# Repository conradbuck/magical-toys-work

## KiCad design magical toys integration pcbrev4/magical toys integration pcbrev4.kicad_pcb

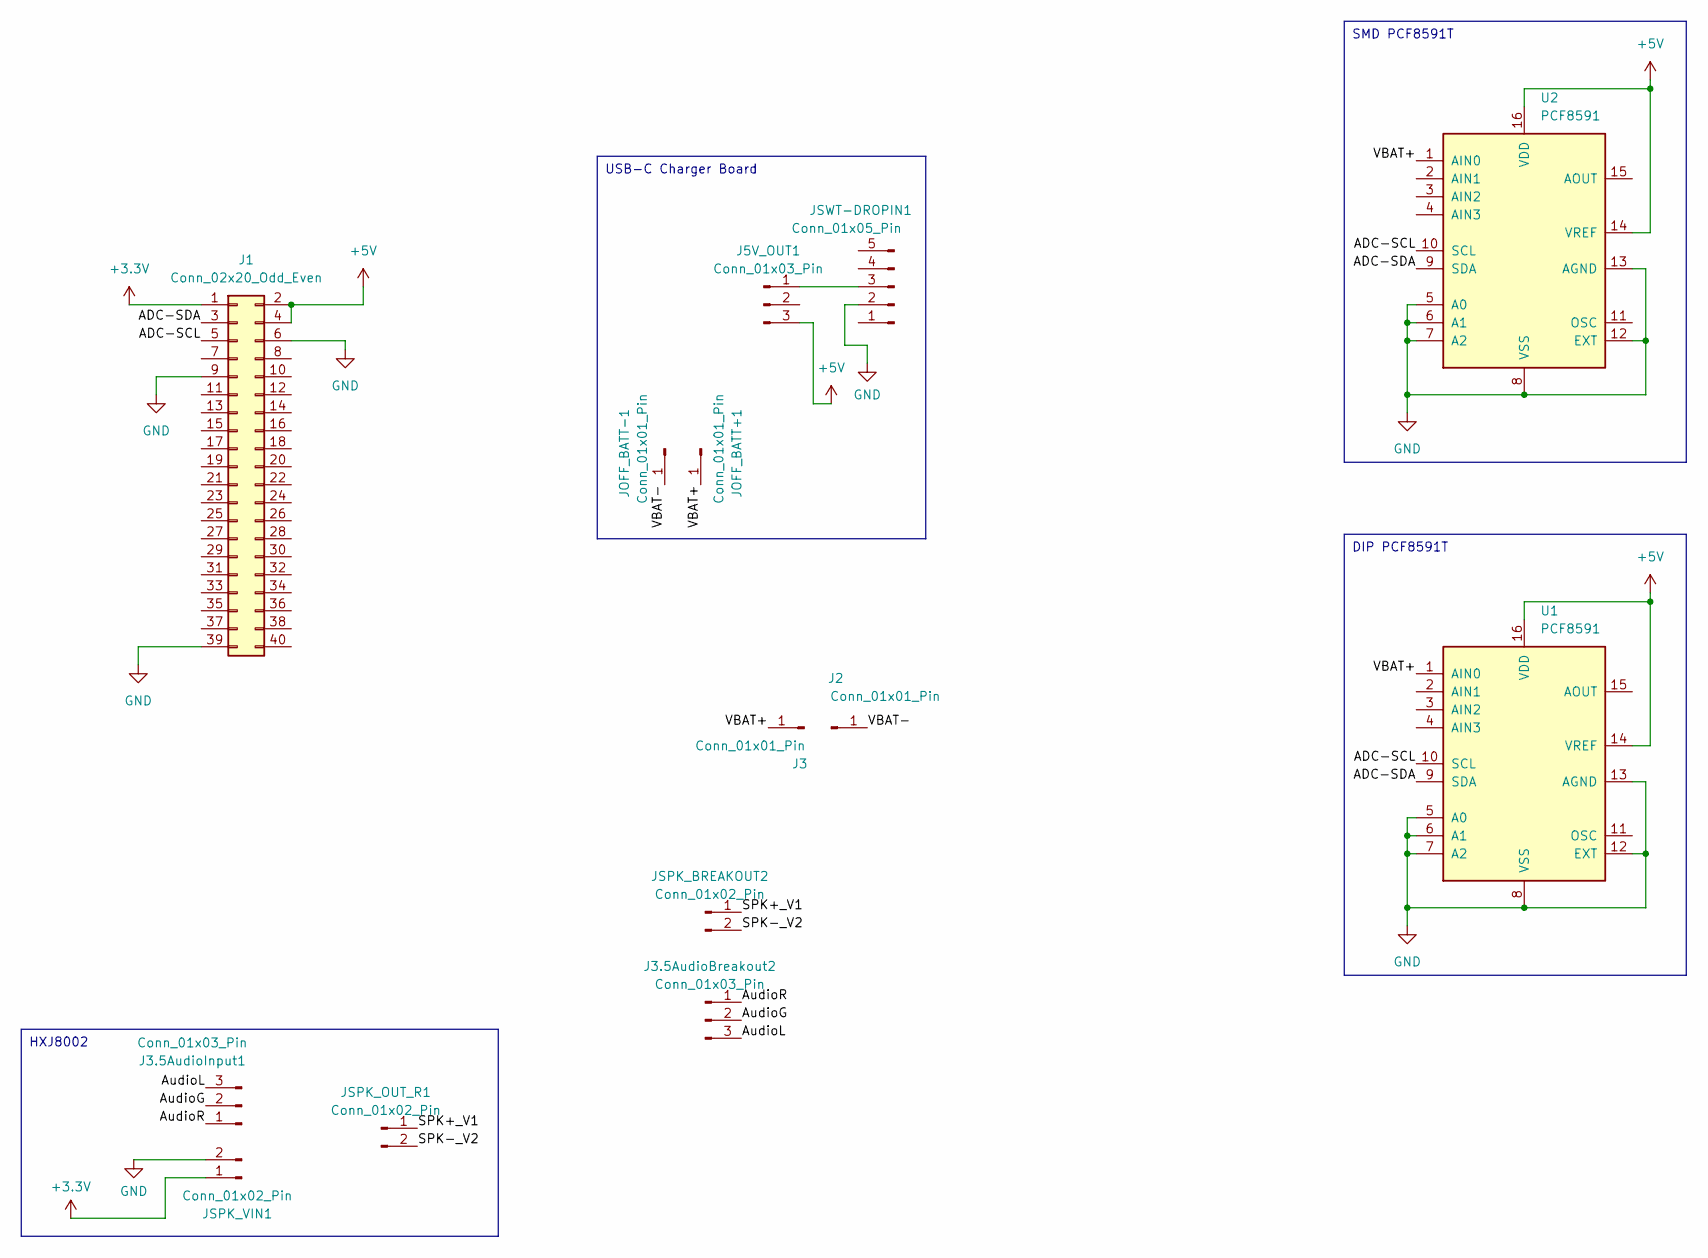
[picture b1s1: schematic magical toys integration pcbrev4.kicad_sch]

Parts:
J1: Conn_02x20_Odd_Even; PinHeader_2x20_P2.54mm_Vertical
J2, J3: Conn_01x01_Pin; SolderWire-1.5sqmm_1x01_D1.7mm_OD3.9mm
J3.5AudioBreakout2, J3.5AudioInput1: Conn_01x03_Pin; PinSocket_1x03_P2.54mm_Vertical
J5V_OUT1: Conn_01x03_Pin; PinHeader_1x03_P2.54mm_Vertical
JOFF_BATT+1: Conn_01x01_Pin; PinHeader_1x01_P2.54mm_Vertical
JOFF_BATT-1: Conn_01x01_Pin; PinHeader_1x01_P2.54mm_Vertical
JSPK_BREAKOUT2: Conn_01x02_Pin; PinSocket_1x02_P2.54mm_Vertical
JSPK_OUT_R1: Conn_01x02_Pin; PinSocket_1x02_P2.54mm_Vertical
JSPK_VIN1: Conn_01x02_Pin; PinSocket_1x02_P2.54mm_Vertical
JSWT-DROPIN1: Conn_01x05_Pin; PinHeader_1x05_P2.54mm_Vertical
U1: PCF8591; DIP-16_W7.62mm_Socket
U2: PCF8591; SOIC127P1032X265-16N

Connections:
+3.3V: J1.1, JSPK_VIN1.1
+5V: J1.2, J1.4, J5V_OUT1.3, U1.14 (VREF), U1.16 (VDD), U2.14 (VREF), U2.16 (VDD)
/ADC-SCL: J1.5, U1.10 (SCL), U2.10 (SCL)
/ADC-SDA: J1.3, U1.9 (SDA), U2.9 (SDA)
/AudioG: J3.5AudioBreakout2.2, J3.5AudioInput1.2
/AudioL: J3.5AudioBreakout2.3, J3.5AudioInput1.3
/AudioR: J3.5AudioBreakout2.1, J3.5AudioInput1.1
/SPK+_V1: JSPK_BREAKOUT2.1, JSPK_OUT_R1.1
/SPK-_V2: JSPK_BREAKOUT2.2, JSPK_OUT_R1.2
/VBAT+: J3.1, JOFF_BATT+1.1, U1.1 (AIN0), U2.1 (AIN0)
/VBAT-: J2.1, JOFF_BATT-1.1
GND: J1.6, J1.9, J1.39, JSPK_VIN1.2, JSWT-DROPIN1.2, U1.5 (A0), U1.6 (A1), U1.7 (A2), U1.8 (VSS), U1.12 (EXT), U1.13 (AGND), U2.5 (A0), U2.6 (A1), U2.7 (A2), U2.8 (VSS), U2.12 (EXT), U2.13 (AGND)
unnamed: J5V_OUT1.1, JSWT-DROPIN1.3

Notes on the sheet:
USB-C Charger Board
SMD PCF8591T
DIP PCF8591T
HXJ8002

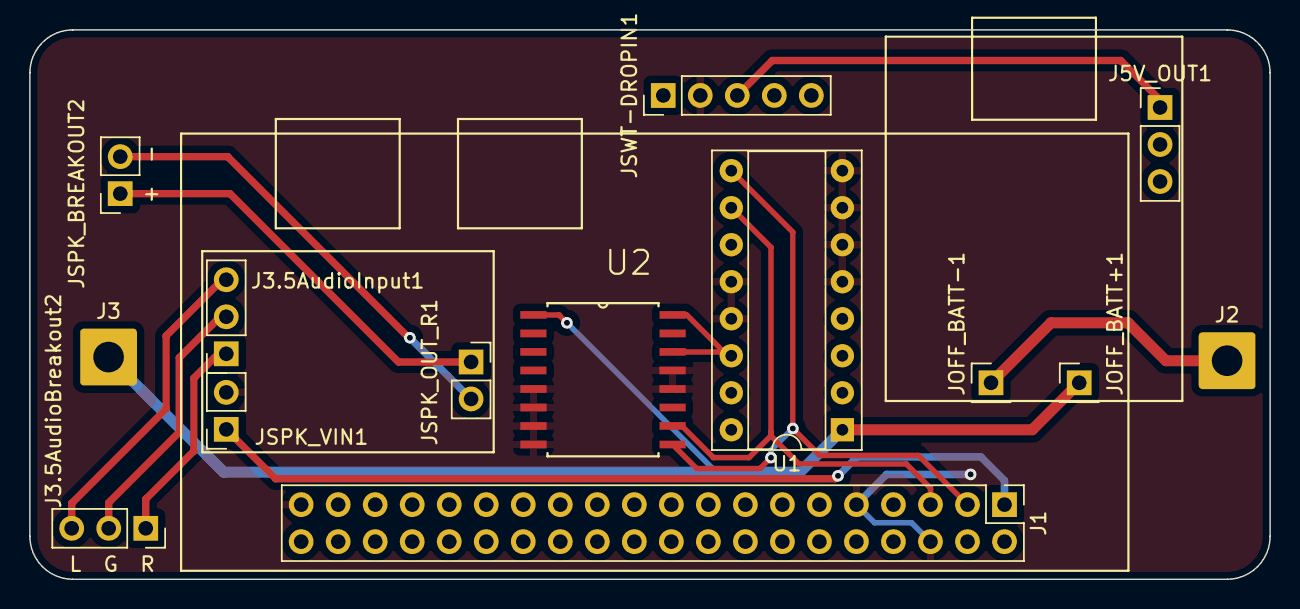
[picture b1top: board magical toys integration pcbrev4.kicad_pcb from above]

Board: 2 copper layers, 85.1 x 37.7 mm, 14 parts (0 on the bottom side), 13 nets.

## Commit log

2024-11-01 posting to GitHub to share my work
2024-11-01 added screenshot of rev4 pcb
